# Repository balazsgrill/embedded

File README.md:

embedded
========

My embedded projects

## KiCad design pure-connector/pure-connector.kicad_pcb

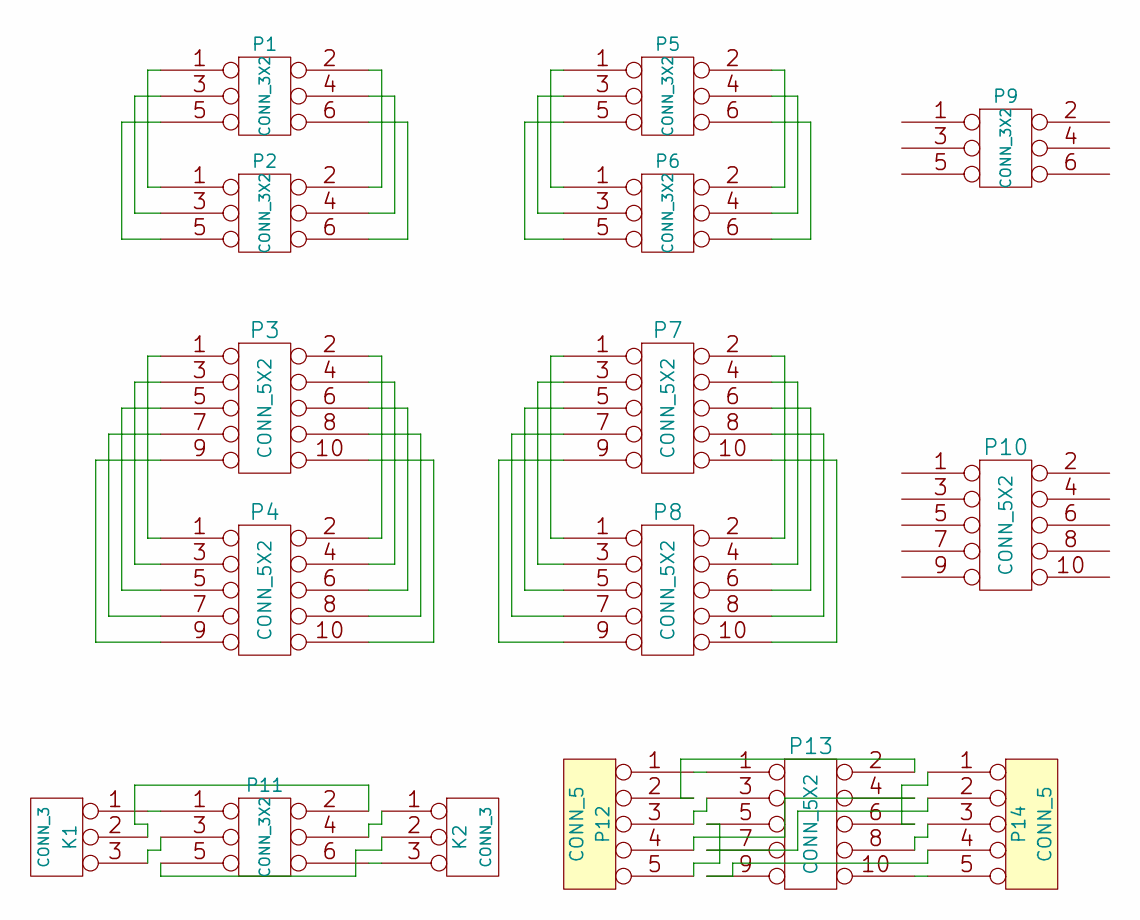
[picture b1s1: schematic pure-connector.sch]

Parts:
K1, K2: CONN_3
P1, P2, P5, P6, P9, P11: CONN_3X2
P3, P4, P7, P8, P10, P13: CONN_5X2
P12, P14: CONN_5

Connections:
unnamed: K2.3, P11.6
unnamed: P13.6, P14.1
unnamed: P13.10, P14.5
unnamed: K1.1, P11.1
unnamed: K1.2 (PM), P11.2
unnamed: P7.1, P8.1
unnamed: P5.6, P6.6
unnamed: P7.4, P8.4
unnamed: P7.6, P8.6
unnamed: P7.8, P8.8
unnamed: P7.10, P8.10
unnamed: K1.3, P11.3
unnamed: P7.3, P8.3
unnamed: P7.5, P8.5
unnamed: P7.7, P8.7
unnamed: P7.9, P8.9
unnamed: P12.2, P13.2
unnamed: P12.3, P13.3
unnamed: P12.4, P13.4
unnamed: P12.5, P13.5
unnamed: P13.7, P14.2
unnamed: P13.8, P14.3
unnamed: P13.9, P14.4
unnamed: K2.1, P11.4
unnamed: K2.2 (PM), P11.5
unnamed: P12.1, P13.1
unnamed: P1.3, P2.3
unnamed: P1.4, P2.4
unnamed: P1.2, P2.2
unnamed: P1.5, P2.5
unnamed: P1.1, P2.1
unnamed: P3.2, P4.2
unnamed: P1.6, P2.6
unnamed: P3.4, P4.4
unnamed: P3.6, P4.6
unnamed: P3.8, P4.8
unnamed: P3.10, P4.10
unnamed: P3.5, P4.5
unnamed: P3.1, P4.1
unnamed: P3.3, P4.3
unnamed: P3.7, P4.7
unnamed: P3.9, P4.9
unnamed: P7.2, P8.2
unnamed: P5.1, P6.1
unnamed: P5.3, P6.3
unnamed: P5.5, P6.5
unnamed: P5.2, P6.2
unnamed: P5.4, P6.4

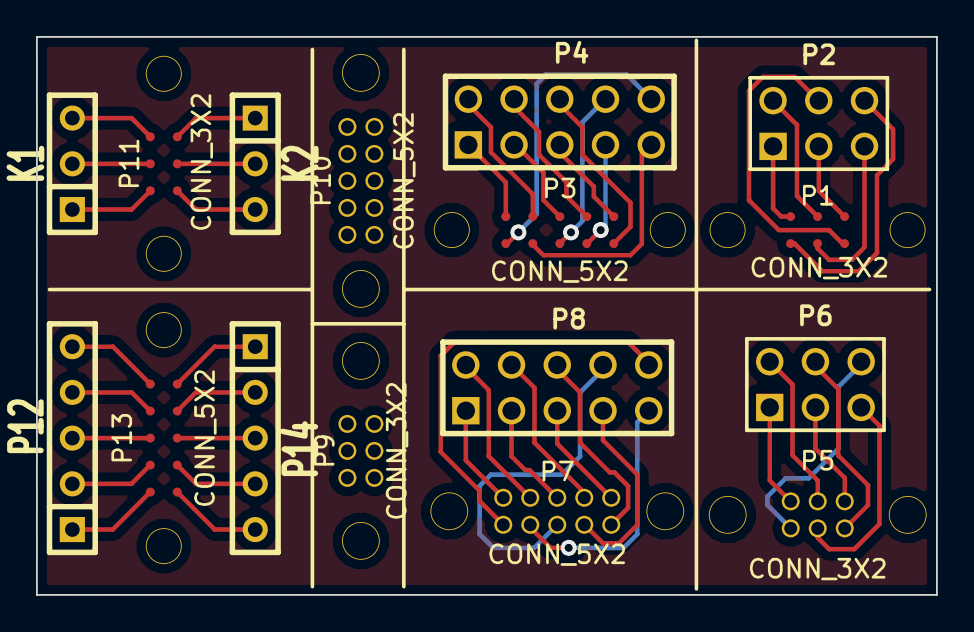
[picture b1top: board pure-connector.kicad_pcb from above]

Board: 2 copper layers, 50.0 x 31.0 mm, 16 parts (0 on the bottom side), 48 nets.

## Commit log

2013-10-29 MSP430FR5739 sample project built with MSPGCC
2013-10-30 Linking did not include interrupt vector table modifed cc call to not only compile, but to link also. Output tested on target successfully.
2013-10-31 eSwitch started
2013-11-05 electronic switch actuator schematic
2014-01-23 hac0202-u1 embedded code
2014-01-24 pre-settings
2014-01-24 uart test continued
2014-01-27 UART loopback test is successful
2014-02-04 Project ported to XC8 compiler
2014-02-06 relay control implemented
2014-02-06 controller servlet started
2014-02-06 restructured repository
2014-02-07 restructured code, planned to make it somewhat portable
2014-02-08 Make structure now can build project with XC8 outside of mplabx
2014-02-08 deleted netbeans and mplab project descriptor files
2014-02-09 Relay2 works through web servlet
2014-02-10 Actuator PWM control implemented
2014-02-11 Servlet refactored
2014-02-12 Drive ramping fixed
2014-02-13 Create gh-pages branch via GitHub
2014-02-18 Controller page added, service thread made more robust
2014-02-22 Relay2 device control was inverted
2014-02-27 Message statistics are collected
2014-02-27 fix NPE
2014-02-28 removed unnecessary sysout
2014-03-01 queue length added to stats
2014-03-01 measuring actual control period
2014-03-01 minor adustments
2014-03-01 timeout signaling
2014-03-12 trying to recover from persistent errors
2014-03-12 properly disconnect
2014-03-12 minor fix
2014-03-26 implementing hac0202 server-side connection as a native app
2014-03-26 minor modification
2014-04-22 Generic control webapp with generator
2014-04-23 HAC servlet generator improved
2014-04-23 generator called from ant script
2014-04-25 Control page calls hac0202ctrl
2014-05-06 Button item generates as anchor instead of form
2014-06-03 pogo-pin connector design
2014-07-22 Pump drive code first draft
2014-08-18 PumpDriver finished
2014-08-26 Ethernet-Can gateway initial code upload
2014-08-27 periodical redraw
2014-09-05 added more information to display
2014-09-19 control page in php
2014-09-23 modified permissions
2014-10-09 debugging
2014-11-26 OpenVFB definition started
2014-11-28 openvfb continued
2015-01-30 Collecting driver codes
2015-02-25 Created mplabx project
2015-03-04 Using bakefile tool (with xc8 extension)
2015-03-06 test code for i2c communication
2015-04-22 uart-dio started
2015-04-22 uart-dio
2015-04-22 Only read when needed
2015-05-02 uart.dio java interface
2015-05-10 uart-dio MQTT interface
2015-05-10 minor changes
2015-05-10 Added simple connection test
2015-05-10 Added some tests
2015-05-10 deleted unnecesssary files
2015-05-11 sending heartbeat signal
